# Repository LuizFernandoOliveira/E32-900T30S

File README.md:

# E32-900T30S Shield
 LoRa IoT Module

Electronic circuit designed to communicate between the E32-900T30S module and a microcontrolled/embedded system.

- The J1 connector is designed to fit into a Raspberry Pi.
- The J2 connector was designed to be used on a breadboard.
- The J3 connector was designed to be used with other projects (by the author) that have this type of connector.
- The control signal "LORA_ON" allows turning the module on and off.
- The GND_ON control signal is a signal sent from another board that enables/disables the board's GND. In this case, resistor R1 must be soldered. If you don't need to control the board's GND, just solder resistor R2.

**Front-view:**

**Back-view:**

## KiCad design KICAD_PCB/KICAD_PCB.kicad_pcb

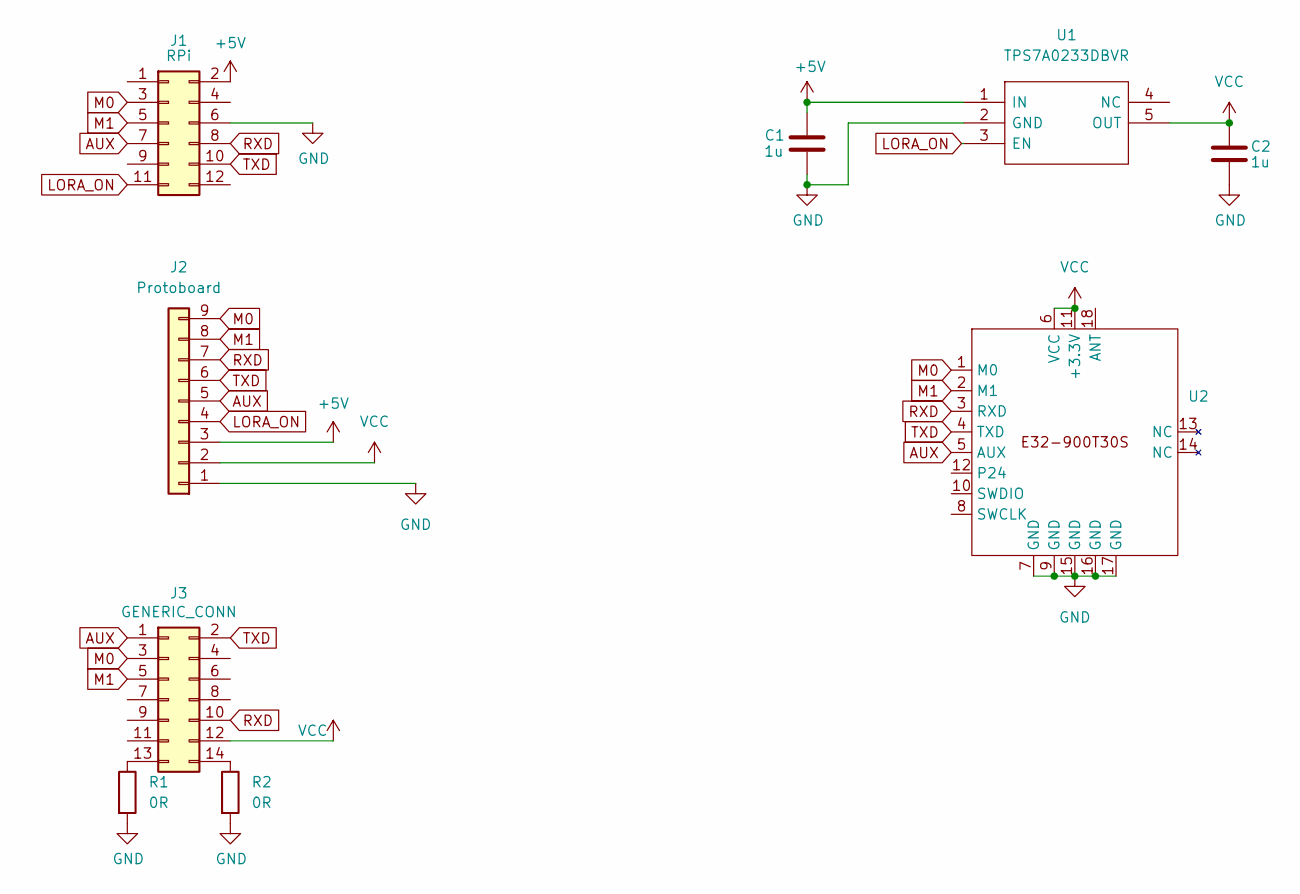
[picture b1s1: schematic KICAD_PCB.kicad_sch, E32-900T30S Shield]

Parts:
C1, C2: 1u; C_0805_2012Metric
J1: RPi; PinSocket_2x06_P2.54mm_Vertical
J2: Protoboard; PinHeader_1x09_P2.54mm_Horizontal
J3: GENERIC_CONN; PinSocket_2x07_P2.54mm_Vertical
R1, R2: 0R; R_0805_2012Metric
U1: TPS7A0233DBVR; SOT-23-5; Manufacturer_Part_Number TPS7A0233DBVR; Mouser Part Number 595-TPS7A0233DBVR
U2: E32-900T30S

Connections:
+5V: C1.1, J1.2, J2.3, U1.1 (IN)
AUX: J1.7, J2.5, J3.1, U2.5 (AUX)
GND: C1.2, C2.2, J1.6, J2.1, R1.2, R2.2, U1.2 (GND), U2.7 (GND), U2.9 (GND), U2.15 (GND), U2.16 (GND), U2.17 (GND)
LORA_ON: J1.11, J2.4, U1.3 (EN)
M0: J1.3, J2.9, J3.3, U2.1 (M0)
M1: J1.5, J2.8, J3.5, U2.2 (M1)
unnamed: J3.13, R1.1
unnamed: J3.14, R2.1
RXD: J1.8, J2.7, J3.10, U2.3 (RXD)
TXD: J1.10, J2.6, J3.2, U2.4 (TXD)
VCC: C2.1, J2.2, J3.12, U1.5 (OUT), U2.6 (VCC), U2.11 (+3.3V)

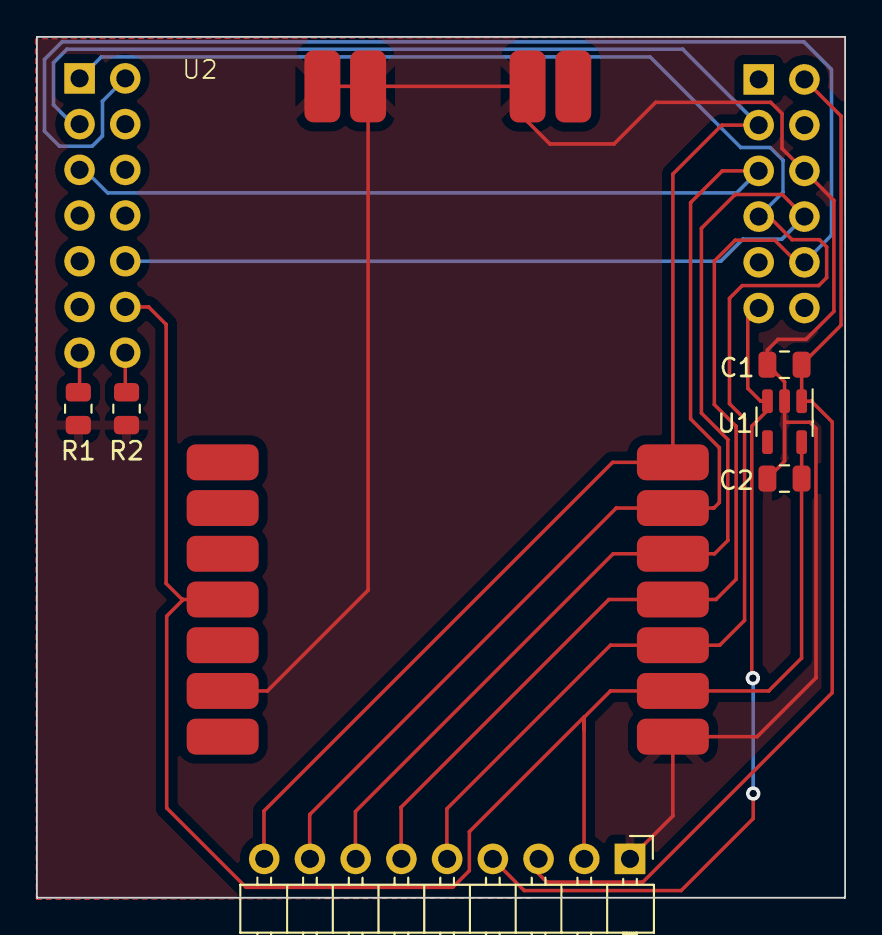
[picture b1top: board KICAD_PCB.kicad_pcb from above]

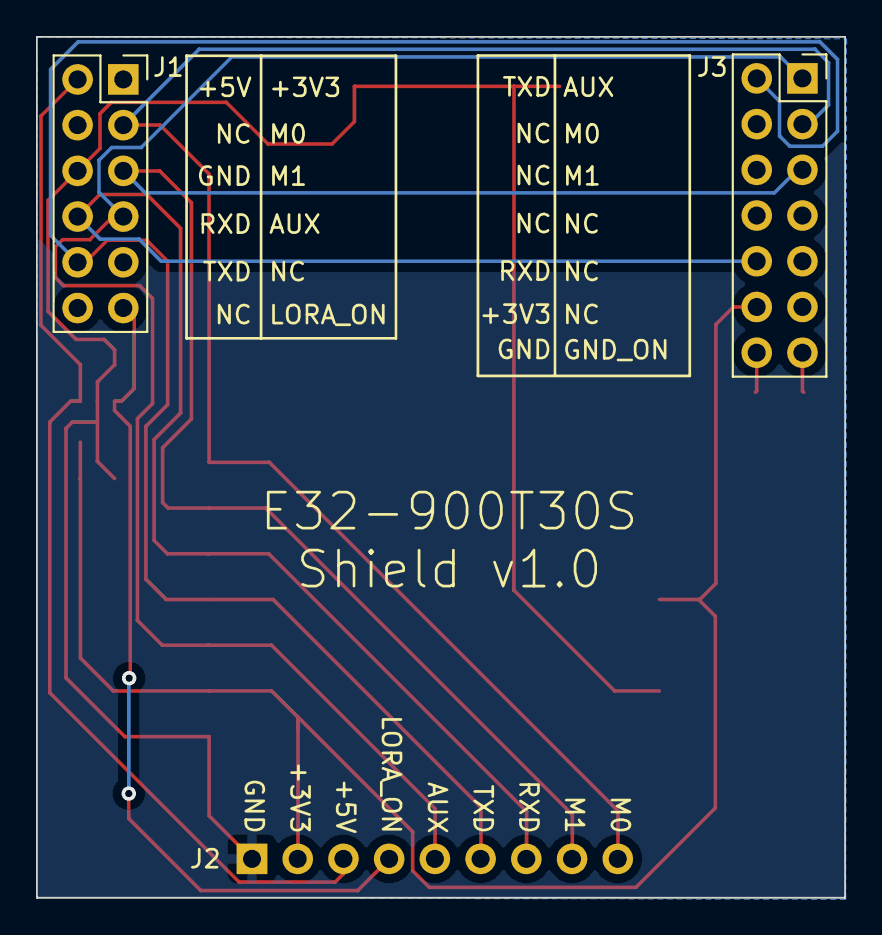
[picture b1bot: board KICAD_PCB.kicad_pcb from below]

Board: 2 copper layers, 44.9 x 47.8 mm, 9 parts (2 on the bottom side), 11 nets.

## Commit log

2024-01-28 Adição do conector genérico J3
2024-01-28 Atualização
